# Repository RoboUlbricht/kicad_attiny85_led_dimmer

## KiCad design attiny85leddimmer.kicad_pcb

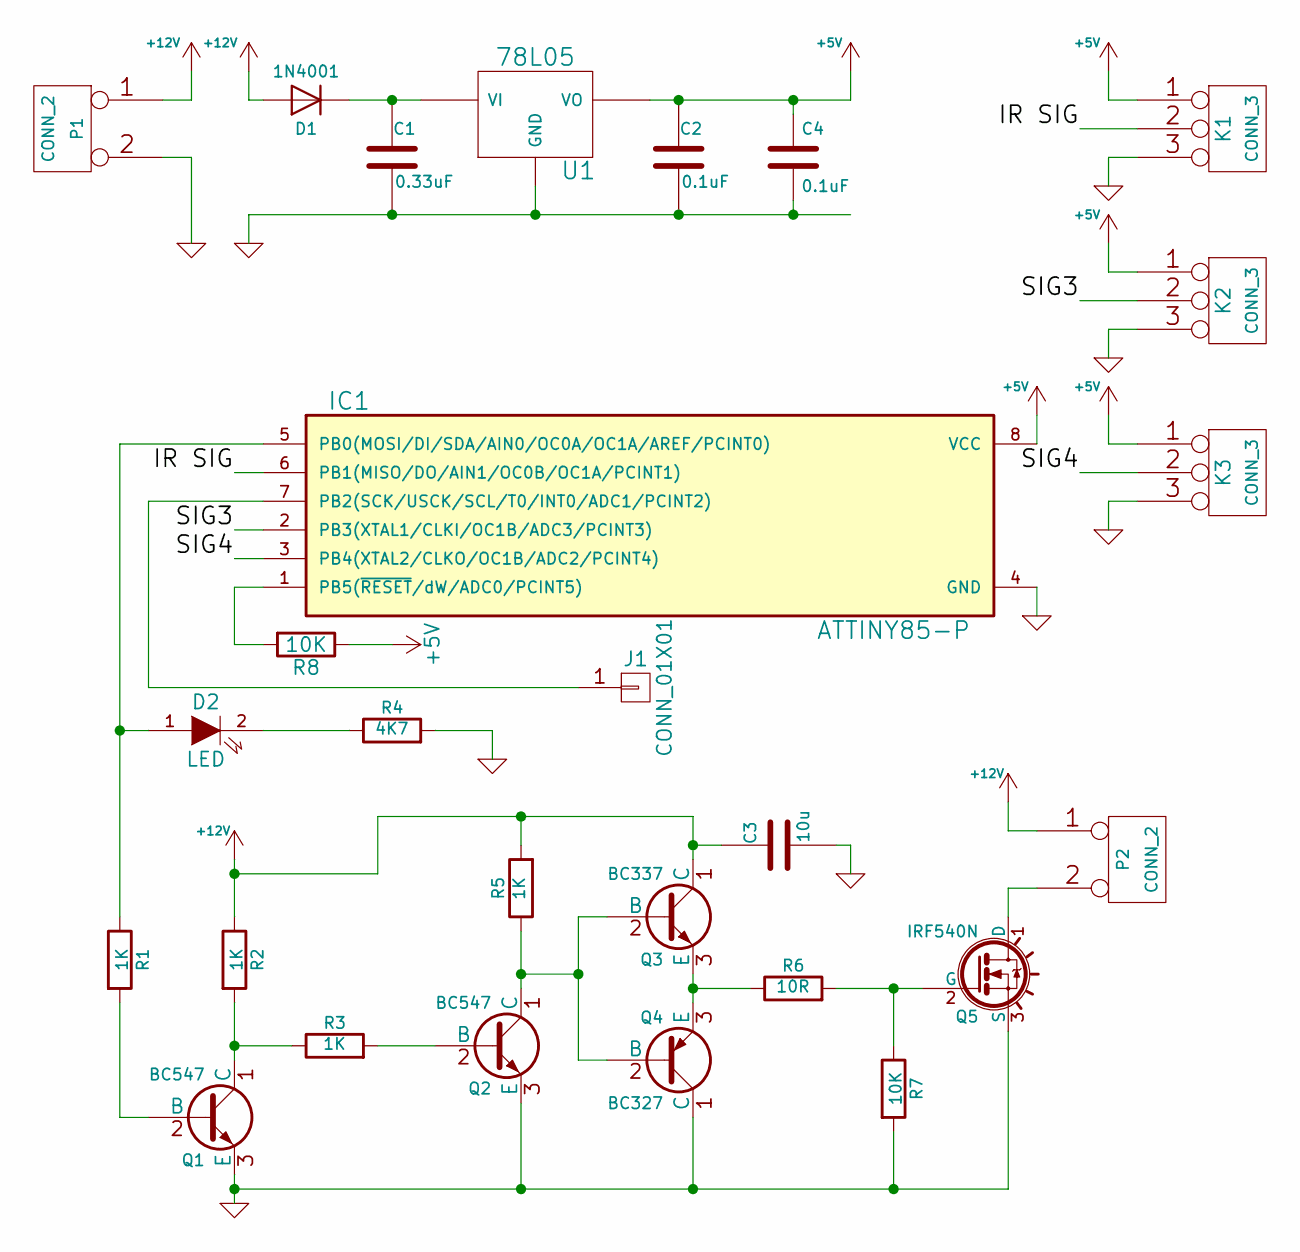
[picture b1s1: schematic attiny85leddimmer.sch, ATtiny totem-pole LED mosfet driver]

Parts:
C1: 0.33uF; C_Disc_D4.3mm_W1.9mm_P5.00mm
C2, C4: 0.1uF; C_Disc_D4.3mm_W1.9mm_P5.00mm
C3: 10u; CP_Radial_D8.0mm_P5.00mm
D1: 1N4001; D_5W_P10.16mm_Horizontal
D2: LED; LED_D5.0mm
IC1: ATTINY85-P; DIP-8_W10.16mm
J1: CONN_01X01; Pin_Header_Straight_1x01_Pitch2.54mm
K1, K2, K3: CONN_3; Pin_Header_Straight_1x03_Pitch2.54mm
P1, P2: CONN_2; bornier2
Q1, Q2: BC547; TO-92_Inline_Wide
Q3: BC337; TO-92_Inline_Wide
Q4: BC327; TO-92_Inline_Wide
Q5: IRF540N; TO-220_Vertical
R1, R2, R3, R5: 1K; R_Axial_DIN0207_L6.3mm_D2.5mm_P10.16mm_Horizontal
R4: 4K7; R_Axial_DIN0207_L6.3mm_D2.5mm_P10.16mm_Horizontal
R6: 10R; R_Axial_DIN0207_L6.3mm_D2.5mm_P10.16mm_Horizontal
R7, R8: 10K; R_Axial_DIN0207_L6.3mm_D2.5mm_P10.16mm_Horizontal
U1: 78L05; TO-92_Inline_Wide

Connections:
+5V: C2.1, C4.1, IC1.8 (VCC), K1.1, K2.1, K3.1, R8.1, U1.VO
+12V: C3.1, D1.2 (A), P1.1, P2.1, Q3.1 (C), R2.1, R5.2
/IR SIG: IC1.6 (PB1(MISO/DO/AIN1/OC0B/OC1A/PCINT1)), K1.2 (PM)
/SIG3: IC1.2 (PB3(XTAL1/CLKI/OC1B/ADC3/PCINT3)), K2.2 (PM)
/SIG4: IC1.3 (PB4(XTAL2/CLKO/OC1B/ADC2/PCINT4)), K3.2 (PM)
GND: C1.2, C2.2, C3.2, C4.2, IC1.4 (GND), K1.3, K2.3, K3.3, P1.2 (PM), Q1.3 (E), Q2.3 (E), Q4.1 (C), Q5.3 (S), R4.2, R7.2, U1.GND
unnamed: C1.1, D1.1 (K), U1.VI
unnamed: D2.1 (A), IC1.5 (PB0(MOSI/DI/SDA/AIN0/OC0A/OC1A/AREF/PCI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), R1.1
unnamed: D2.2 (K), R4.1
unnamed: IC1.1 (PB5(~RESET~/dW/ADC0/PCINT5)), R8.2
unnamed: IC1.7 (PB2(SCK/USCK/SCL/T0/INT0/ADC1/PCINT2)), J1.1
unnamed: P2.2 (PM), Q5.1 (D)
unnamed: Q1.1 (C), R2.2, R3.1
unnamed: Q1.2 (B), R1.2
unnamed: Q2.1 (C), Q3.2 (B), Q4.2 (B), R5.1
unnamed: Q2.2 (B), R3.2
unnamed: Q3.3 (E), Q4.3 (E), R6.1
unnamed: Q5.2 (G), R6.2, R7.1

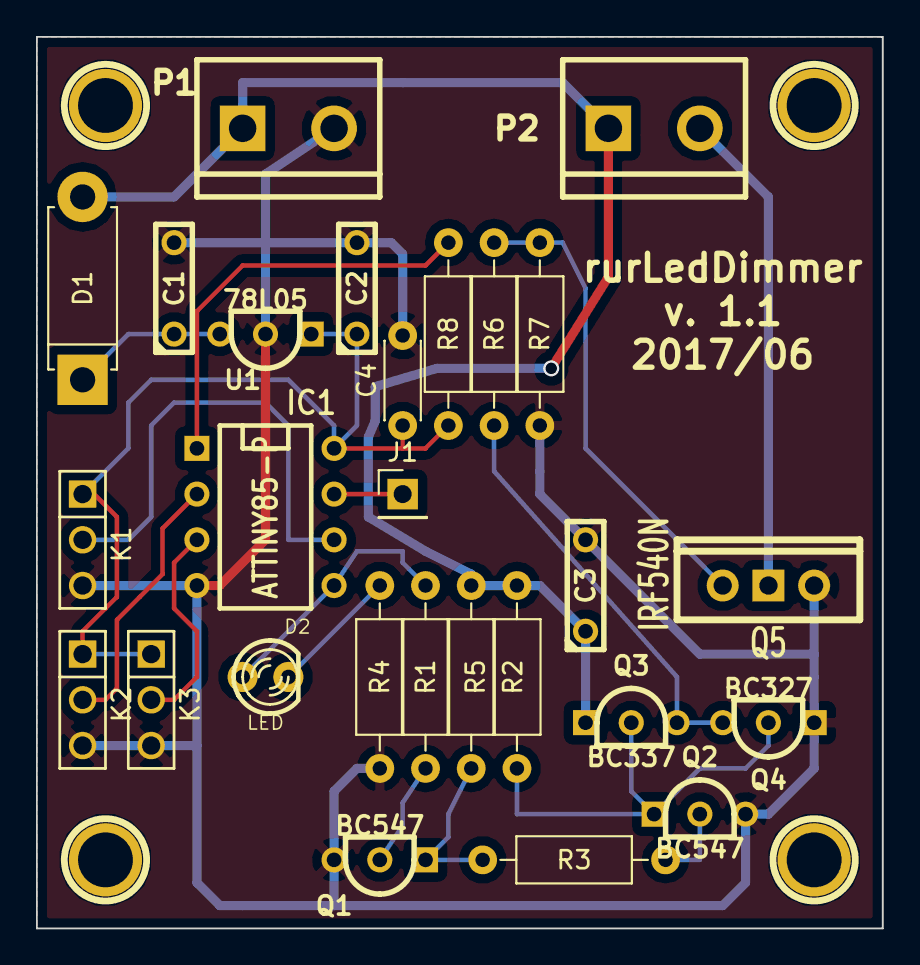
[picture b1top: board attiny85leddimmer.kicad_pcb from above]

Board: 2 copper layers, 47.0 x 49.5 mm, 31 parts (0 on the bottom side), 18 nets.

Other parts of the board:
1PIN, 1PIN#2, 1PIN#3, 1PIN#4: P***; 1pin

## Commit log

2017-06-04 ZIP files
